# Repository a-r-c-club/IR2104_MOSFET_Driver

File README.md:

# Motor Driver
This repository contains all designs for motor driver designs made at VIIT Robotics.
## Design 1 : Comparator Design
This design contains a comparator and a totempole transistor configuration to drive paired N-channel and P-channel MOSFETs without bootstrap capacitors. The file names containing "mosfetdrivercomparator" are the files related to this design. 
## Design 2 : Bootstrap Capacitor Design
This design contains a gate driver IC named IR2104 which drives all N-channel MOSFETs in the H-bridge using a bootstrap capacitor. The file names containing "mosfet driver" are the files related to this design. Even all the Gerber and SVG files are related to this design. It is designed to be manufactured on industrial grades.

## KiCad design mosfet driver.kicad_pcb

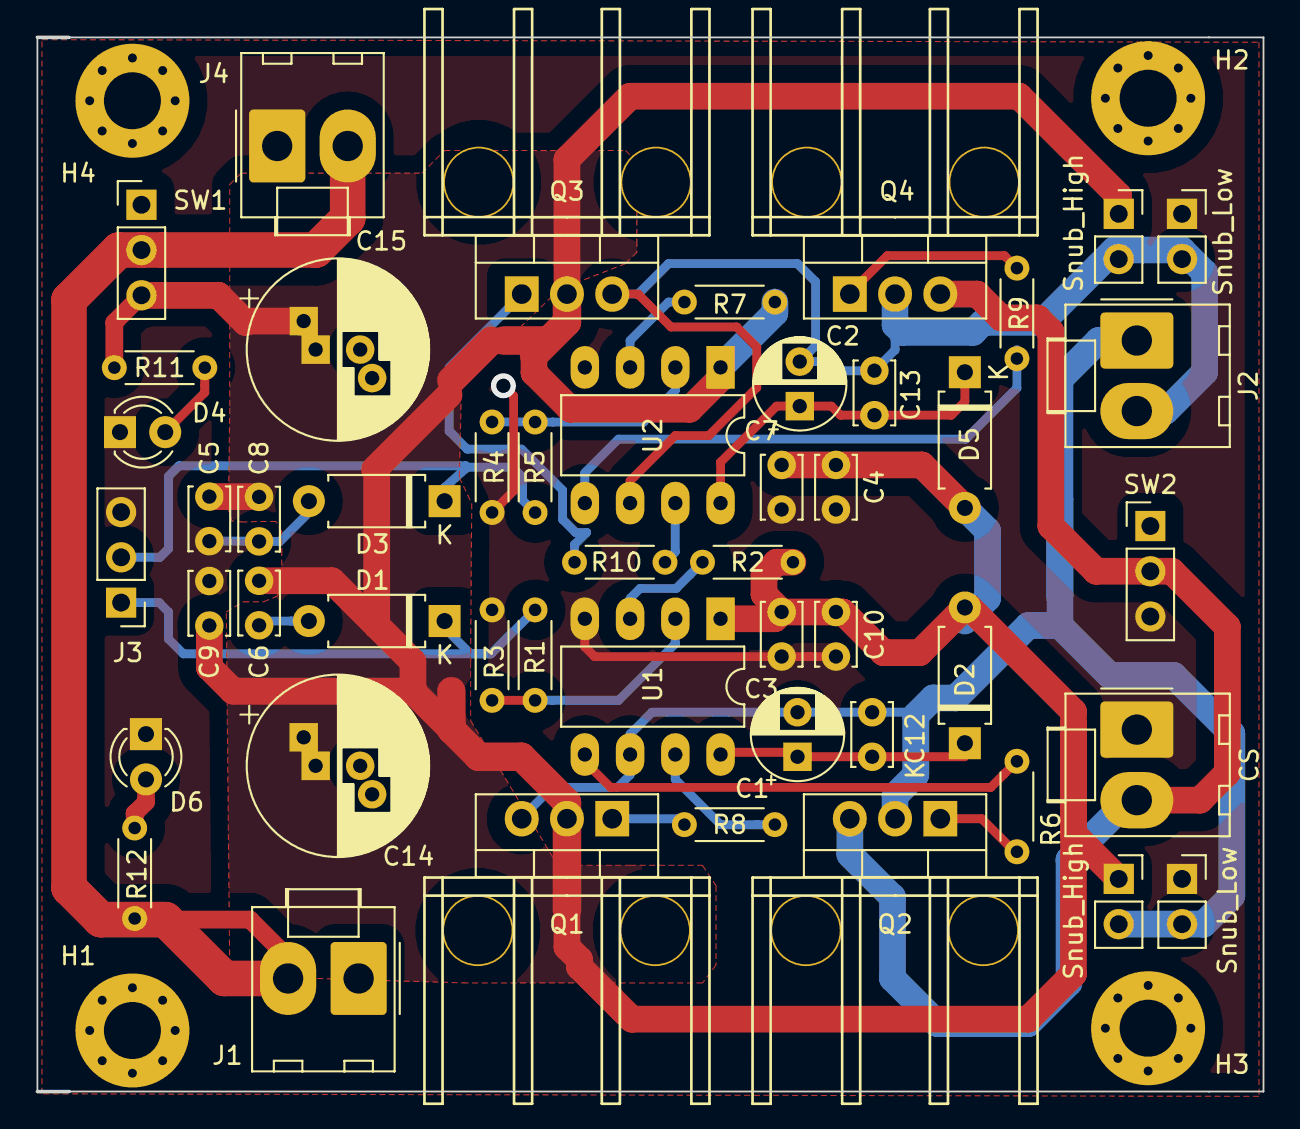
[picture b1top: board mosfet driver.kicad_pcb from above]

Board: 2 copper layers, 68.8 x 59.2 mm, 53 parts (0 on the bottom side), 23 nets.

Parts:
C1, C2: BTSTRP; CP_Radial_D5.0mm_P2.50mm
C3, C4, C5, C6, C12, C13: 0.1uF; C_Disc_D3.4mm_W2.1mm_P2.50mm
C7, C8, C9, C10: 1uF; C_Disc_D3.4mm_W2.1mm_P2.50mm
C14, C15: 270uF/35V; CP_Radial_D10.0mm_P2.50mm_P5.00mm
CS: Molex_KK-396_A-41791-0002_1x02_P3.96mm_Vertical
D1, D3: 5.1 Zener; D_A-405_P7.62mm_Horizontal
D2, D5: 1N4148; D_A-405_P7.62mm_Horizontal
D4, D6: LED; LED_D3.0mm
H1, H2, H3, H4: MountingHole; MountingHole_3.2mm_M3_Pad_Via
J1, J4: PWR_IN; Molex_KK-396_A-41791-0002_1x02_P3.96mm_Vertical
J2: Screw_Terminal_01x02; Molex_KK-396_A-41791-0002_1x02_P3.96mm_Vertical
J3: Conn_01x03_Male; PinHeader_1x03_P2.54mm_Vertical
Q1, Q2, Q3, Q4: IRF3205; heatsinknew
R1, R5: 1K; R_Axial_DIN0204_L3.6mm_D1.6mm_P5.08mm_Horizontal
R2, R7: 10K; R_Axial_DIN0204_L3.6mm_D1.6mm_P5.08mm_Horizontal
R3, R4, R6, R8, R9, R10: 10; R_Axial_DIN0204_L3.6mm_D1.6mm_P5.08mm_Horizontal
R11, R12: 1k; R_Axial_DIN0204_L3.6mm_D1.6mm_P5.08mm_Horizontal
SW1: SW_DIP_x01; PinHeader_1x03_P2.54mm_Vertical
SW2: PinHeader_1x03_P2.54mm_Vertical
Snub_High: PinSocket_1x02_P2.54mm_Vertical
Snub_High#2: PinSocket_1x02_P2.54mm_Vertical
Snub_Low: PinSocket_1x02_P2.54mm_Vertical
Snub_Low#2: PinSocket_1x02_P2.54mm_Vertical
U1, U2: IR2104; DIP-8_W7.62mm_LongPads

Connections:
/Power3: C1.2, C12.2, J2.1, Q1.3, Q2.2, Snub_High.2, Snub_Low.2, U1.6
/Power4: C2.2, C13.2, J2.2, Q3.3, Q4.2, Snub_High#2.2, Snub_Low#2.2, U2.6
/Signal: D1.1, J3.1, R1.2
/Signal2: D3.1, J3.2, R5.2
GND: C3.2, C4.2, C5.2, C6.2, C7.2, C8.2, C9.2, C10.2, C14.2, C15.2, CS.1, D1.2, D3.2, D4.1, D6.1, J1.1, J3.3, J4.1, R3.2, R4.2, SW2.3, Snub_Low.1, Snub_Low#2.1, U1.4, U2.4
unnamed: C1.1, C12.1, D2.1, U1.8
unnamed: C2.1, C13.1, D5.1, U2.8
unnamed: D4.2, R11.2
unnamed: D6.2, R12.2
unnamed: J1.2, J4.2, R12.1, SW1.2
unnamed: Q1.1, R8.1
unnamed: Q2.1, R6.2
unnamed: Q3.1, R10.1
unnamed: Q4.1, R9.2
unnamed: R1.1, R3.1, U1.2
unnamed: R2.2, U1.3
unnamed: R4.1, R5.1, U2.2
unnamed: R6.1, U1.5
unnamed: R7.2, U2.3
unnamed: R8.2, U1.7
unnamed: R9.1, U2.5
unnamed: R10.2, U2.7
VCC: C3.1, C4.1, C5.1, C6.1, C7.1, C8.1, C9.1, C10.1, C14.1, C15.1, D2.2, D5.2, Q1.2, Q3.2, R2.1, R7.1, R11.1, SW1.3, Snub_High.1, Snub_High#2.1, U1.1, U2.1

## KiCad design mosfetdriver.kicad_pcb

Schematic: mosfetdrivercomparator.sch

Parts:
C1: 470micro; CP_Radial_D10.0mm_P2.50mm
C2, C3: 0.47micro; CP_Radial_D10.0mm_P2.50mm
D1, D2: LED; LED_D3.0mm
D3, D4: 1N4148; D_DO-35_SOD27_P7.62mm_Horizontal
J1, J4, J5: Conn_01x02_Male; Molex_Mini-Fit_Jr_5566-02A_2x01_P4.20mm_Vertical
J2, J3: Conn_01x03_Male; PinHeader_1x03_P2.54mm_Vertical
OK1, OK2: 4N35; DIL06
Q1, Q4: BC547; TO-92_Inline
Q2, Q3: BC557; TO-92_Inline
Q5, Q8: IRF9540N; heatsink2
Q6, Q7: IRF3205; heatsink2
R1, R2: 220; R_Axial_DIN0207_L6.3mm_D2.5mm_P10.16mm_Horizontal
R3, R5: 470; R_Axial_DIN0207_L6.3mm_D2.5mm_P10.16mm_Horizontal
R4, R6, R7, R8, R9, R10: 10k; R_Axial_DIN0207_L6.3mm_D2.5mm_P10.16mm_Horizontal
R11, R12: 3.3; R_Axial_DIN0207_L6.3mm_D2.5mm_P10.16mm_Horizontal
S1: MINI-SPDT-SW; SW_MINI-SPDT-SW
U1: LM358P; DIP254P762X508-8

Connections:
/base: Q3.2, Q4.2, U1.7
/bat1: J1.2, R5.1, S1.1, S1.2
/bat2: D1.2 (A), R5.2
/emitter: D4.1 (K), Q3.3, Q4.3, R12.2
/fet1: J5.1, Q7.2 (D), Q8.2
/fet2: J5.3, Q5.2, Q6.2 (D)
GND: C1.2, D1.1 (K), D2.1 (K), J1.1, J5.2, OK1.4, OK2.4, Q2.1, Q3.1, Q6.3 (S), Q7.3 (S), R8.2, R9.2, U1.4
GNDD: J2.3, J3.3, OK1.2, OK2.2
unnamed: C2.2, D3.2 (A), Q5.1, Q6.1 (G), R11.1
unnamed: C3.2, D4.2 (A), Q7.1 (G), Q8.1, R12.1
unnamed: D2.2 (A), R3.2
unnamed: D3.1 (K), Q1.3, Q2.3, R11.2
unnamed: J2.1, J3.1, R1.2
unnamed: J2.2, J3.2, R2.1
unnamed: OK1.1, R2.2
unnamed: OK1.5, R7.2, U1.6
unnamed: OK2.1, R1.1
unnamed: OK2.5, R4.1, U1.2
unnamed: Q1.2, Q2.2, U1.1
unnamed: R6.1, R9.1, U1.5
unnamed: R8.1, R10.2, U1.3
VCC: C1.1, C2.1, C3.1, Q1.1, Q4.1, Q5.3, Q8.3, R3.1, R4.2, R6.2, R7.1, R10.1, S1.3, U1.8

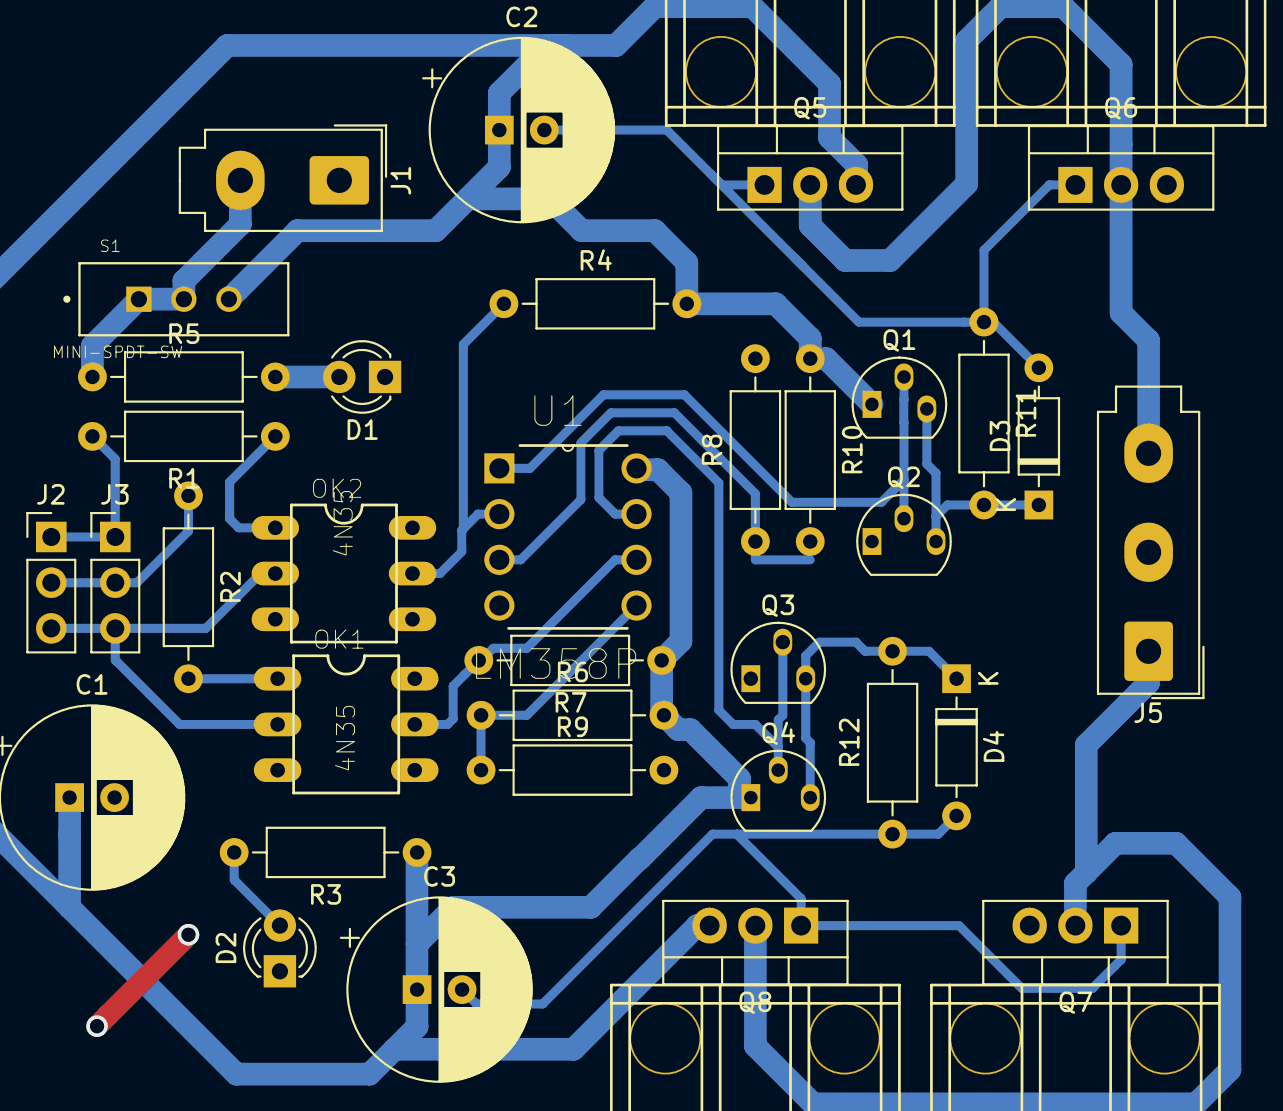
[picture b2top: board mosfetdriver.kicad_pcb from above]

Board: 2 copper layers, 35 parts (0 on the bottom side), 22 nets.

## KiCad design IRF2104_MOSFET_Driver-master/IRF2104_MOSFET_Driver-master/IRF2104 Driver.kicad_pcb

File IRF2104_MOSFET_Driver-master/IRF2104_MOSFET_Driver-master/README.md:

# IR2104_MOSFET_Driver
IR2104 based MOSFET Driver revised PCB designed by Sudhamshu

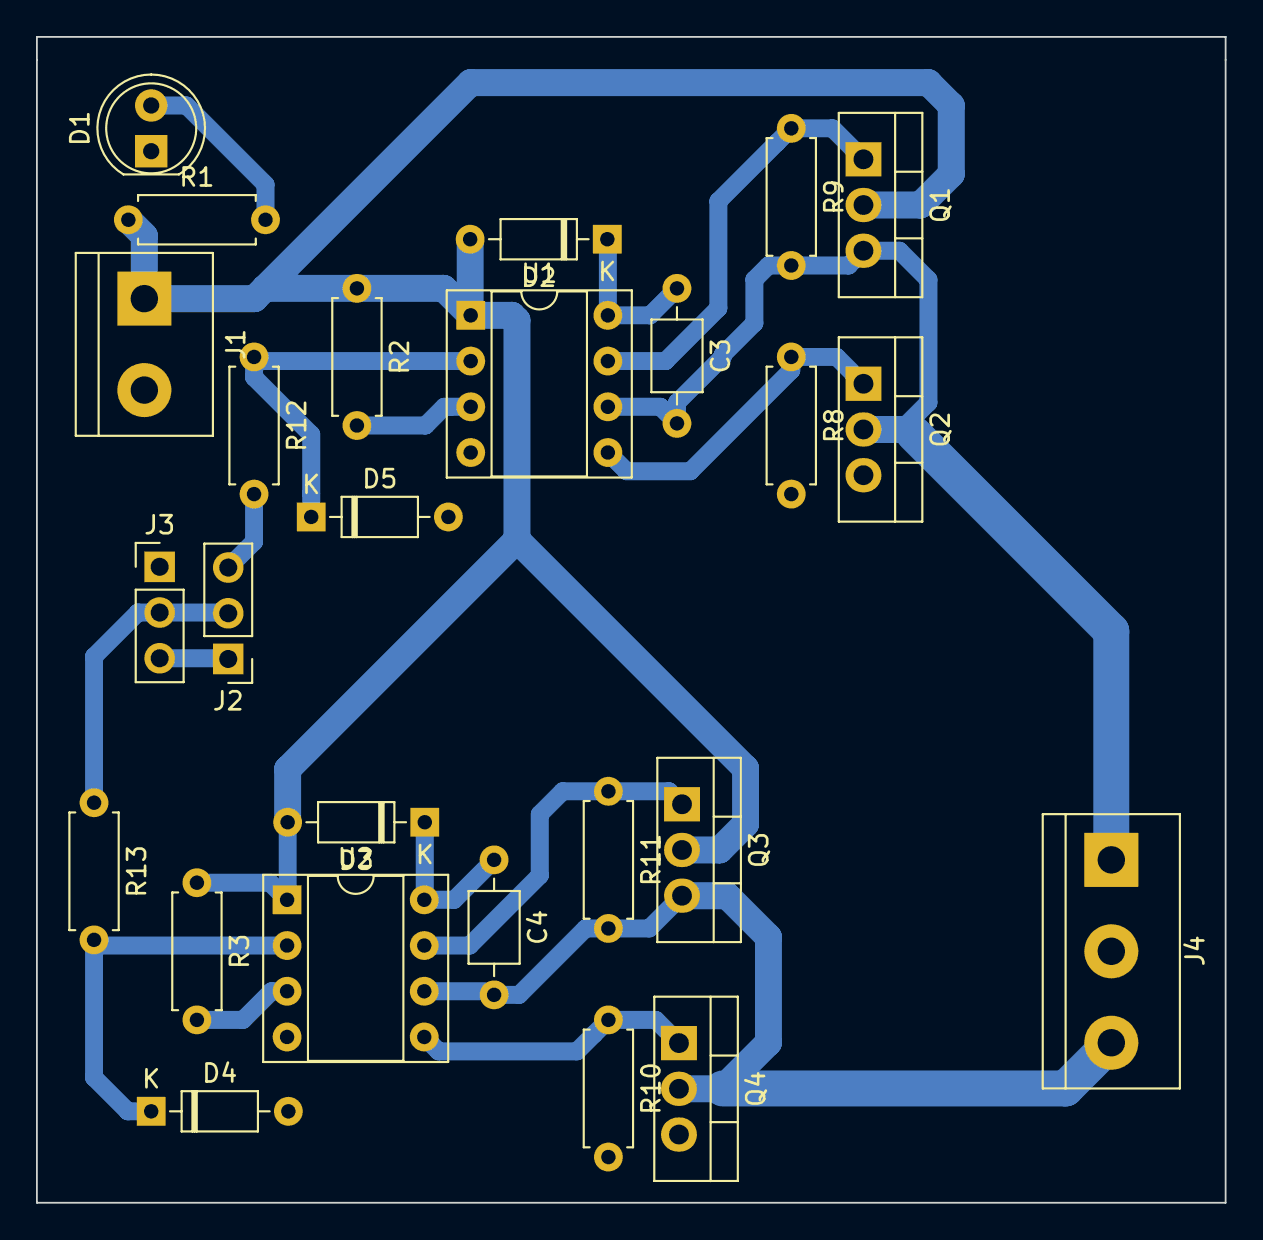
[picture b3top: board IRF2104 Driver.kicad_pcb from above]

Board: 2 copper layers, 66.0 x 64.8 mm, 26 parts (0 on the bottom side), 17 nets.

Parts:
C3, C4: CP1; C_Axial_L3.8mm_D2.6mm_P7.50mm_Horizontal
D1: LED; LED_D5.0mm
D2, D3: 1N4148; D_DO-35_SOD27_P7.62mm_Horizontal
D4, D5: D_Zener; D_DO-35_SOD27_P7.62mm_Horizontal
J1: Screw_Terminal_01x02; TerminalBlock_bornier-2_P5.08mm
J2: Conn_01x03_Female; PinHeader_1x03_P2.54mm_Vertical
J3: Conn_01x03_Male; PinHeader_1x03_P2.54mm_Vertical
J4: Screw_Terminal_01x03; TerminalBlock_bornier-3_P5.08mm
Q1, Q2, Q3, Q4: IRF3205; TO-220-3_Vertical
R1: 5k; R_Axial_DIN0207_L6.3mm_D2.5mm_P7.62mm_Horizontal
R2, R3: 10k; R_Axial_DIN0207_L6.3mm_D2.5mm_P7.62mm_Horizontal
R8, R9, R10, R11, R12, R13: 1k; R_Axial_DIN0207_L6.3mm_D2.5mm_P7.62mm_Horizontal
U1, U2: IR2104; DIP-8_W7.62mm_Socket

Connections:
GND: D1.1, D4.2, D5.2, J1.2, J2.1, J3.3, J4.2, Q2.3, Q4.3, R8.2, R10.2, U1.4, U2.4
unnamed: C3.1, D2.1, U1.8
unnamed: C3.2, J4.1, Q1.3, Q2.2, R9.2, U1.6
unnamed: C4.1, D3.1, U2.8
unnamed: C4.2, J4.3, Q3.3, Q4.2, R11.2, U2.6
unnamed: D1.2, R1.2
unnamed: D4.1, R13.2, U2.2
unnamed: D5.1, R12.1, U1.2
unnamed: J2.2, J3.2, R13.1
unnamed: J2.3, J3.1, R12.2
unnamed: Q1.1, R9.1, U1.7
unnamed: Q2.1, R8.1, U1.5
unnamed: Q3.1, R11.1, U2.7
unnamed: Q4.1, R10.1, U2.5
unnamed: R2.2, U1.3
unnamed: R3.2, U2.3
VCC: D2.2, D3.2, J1.1, Q1.2, Q3.2, R1.1, R2.1, R3.1, U1.1, U2.1

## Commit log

2019-10-25 Resistor issue fixed
2020-03-11 Design for manufacturing double sided PCB
    This does not however contain any passive components which are needed for filtering input not output. This isn't final yet.
2020-03-11 Input and output filters added
    Changes suggested by Malhar implemented. Input and output filters added. Output for current sensor added. MOLEX connector outputs added. LED added. Switches added.
2020-03-11 Current Sensor placement solved
    Switch for current sensor added for bypassing it whenever unnecessary. This board is also tailored for manufacturing in-house.
2020-03-11 Discarded Old Design
2020-03-11 Files in the wrong branch deleted
2020-03-11 Old Designs removed from Master
2020-03-11 Old design removed from master
2020-03-11 Comparator Design (Modified by Sharwari)
2020-03-11 Wrong files in the branch
2020-03-11 Wrong file in the branch
2020-03-11 Rename mosfetdriver.kicad_pcb to mosfetdrivercomparator.kicad_pcb
2020-03-11 Rename mosfetdriver.pro to mosfetdrivercomparator.pro
2020-03-11 Rename mosfetdriver.sch to mosfetdrivercomparator.sch
2020-03-11 Unnecessary
2020-03-11 Manufacturing quality
    Finalised board. Bypass for current sensor added.
2020-03-11 Gerber for industrial manufacturing
